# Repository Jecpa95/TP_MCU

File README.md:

# TP_MCU

## TP MCU by Kévin OKONSKI et Jérôme DUPOUTS

--------------------------------------------------------------------------------------------------------------------------------------------------------------------

- PB9 est relié à la masse car cette PIN correspond à BOOT0. Ici ont relie à la masse afin que le BOOT se fasse dans la memoire Flash.

--------------------------------------------------------------------------------------------------------------------------------------------------------------------

- Le role de L1, C5 et C7 est de réaliser un filtre passe bas pour éliminer les parasites sur l'alimentation 3.3V. On utilise par la suite cette tension au niveau de VDDA qui est la PIN de l'ADC

--------------------------------------------------------------------------------------------------------------------------------------------------------------------

--------------------------------------------------------------------------------------------------------------------------------------------------------------------

- C'est la première page qui indique les valeurs des condensateurs, mais on retrouve à la page 1 les valeurs typiques : 

--------------------------------------------------------------------------------------------------------------------------------------------------------------------

- C'est à la page 25 que l'on retrouve l'information : 

--------------------------------------------------------------------------------------------------------------------------------------------------------------------

- CS signifie Chip Select et permet d'activer la communication SPI, elle est valide à l'état Bas

--------------------------------------------------------------------------------------------------------------------------------------------------------------------

- la PIN LDAC (latch DAC synchronization input) permet de transféré l'entrée à la sortie du DAC. Lorsque l'entrée est à l'état bas la sortie recopie l'entrée.

--------------------------------------------------------------------------------------------------------------------------------------------------------------------

- Le MCP n'est pas activé car on ne renvoie pas d'information au STM32.

--------------------------------------------------------------------------------------------------------------------------------------------------------------------

- On retrouve les indications du PinOut du connecteur SWD dans la documentation du STlink à la page 17

--------------------------------------------------------------------------------------------------------------------------------------------------------------------

--------------------------------------------------------------------------------------------------------------------------------------------------------------------

- Ces valeurs est une indiquation sur la tailles des différents composants

--------------------------------------------------------------------------------------------------------------------------------------------------------------------

- Les boîtiers Dummy Low Profile Quad Flat Pack (LQFP) sont des types de boitiers de circuit intégré destiné à être directement soudé sur un circuit imprimé.

--------------------------------------------------------------------------------------------------------------------------------------------------------------------

--------------------------------------------------------------------------------------------------------------------------------------------------------------------

- 
on choisit donc un prescaler à 125, (32000000/1000)/256

--------------------------------------------------------------------------------------------------------------------------------------------------------------------

- nous avons choisie les même valeurs que pour TIM2 pour avoir une fréquence d'intéruption de 1kHz, donc le Prescaler vaut 125 et ARR 255

--------------------------------------------------------------------------------------------------------------------------------------------------------------------

La fonction est vide
--------------------------------------------------------------------------------------------------------------------------------------------------------------------

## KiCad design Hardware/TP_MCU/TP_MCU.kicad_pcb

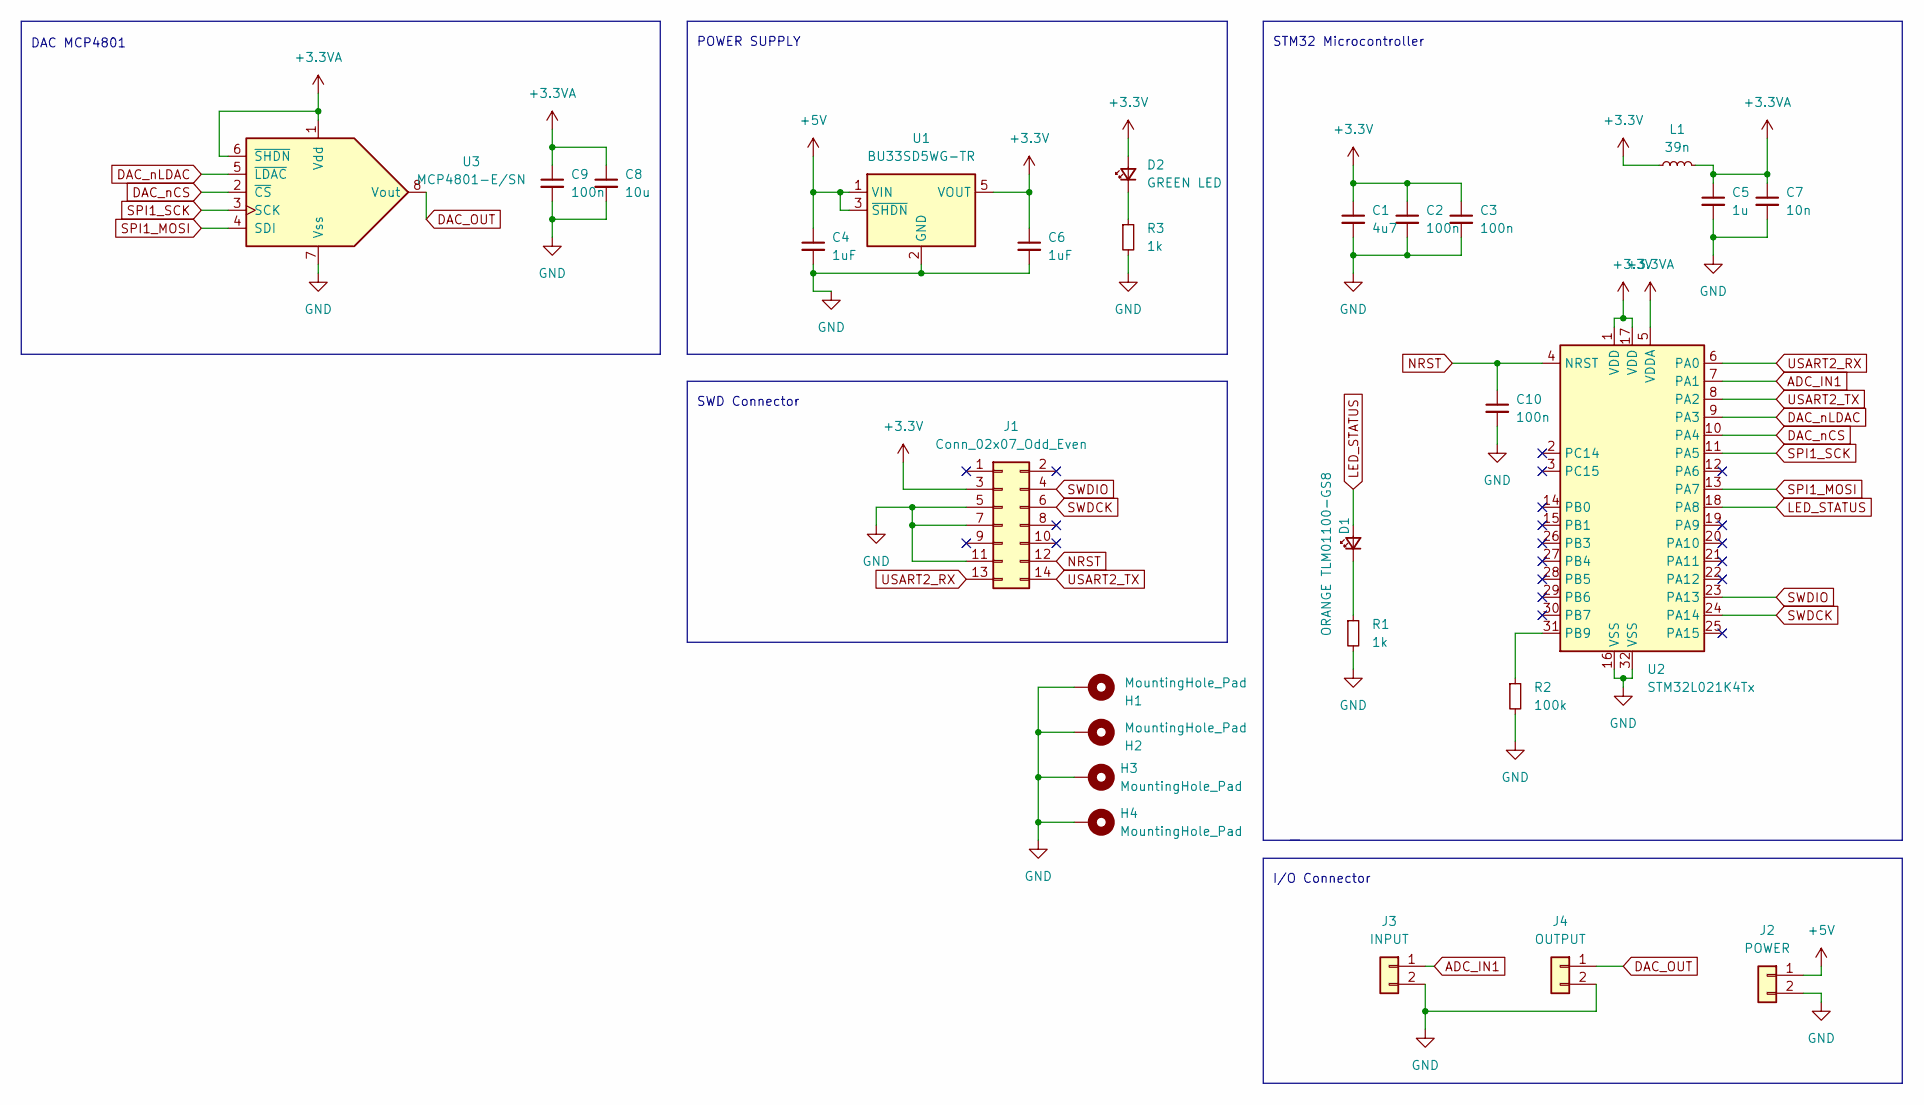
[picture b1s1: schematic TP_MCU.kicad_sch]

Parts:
C1: 4u7; C_0805_2012Metric
C2, C3, C9, C10: 100n; C_0805_2012Metric
C4, C6: 1uF; C_0805_2012Metric
C5: 1u; C_0805_2012Metric
C7: 10n; C_0805_2012Metric
C8: 10u; C_0805_2012Metric
D1: ORANGE TLM01100-GS8; LED_0603_1608Metric
D2: GREEN LED; LED_0603_1608Metric
H1, H2, H3, H4: MountingHole_Pad; MountingHole_3.2mm_M3_Pad
J1: Conn_02x07_Odd_Even; PinHeader_2x07_P1.27mm_Vertical_SMD
J2: POWER; JST_XH_B2B-XH-A_1x02_P2.50mm_Vertical
J3: INPUT; JST_XH_B2B-XH-A_1x02_P2.50mm_Vertical
J4: OUTPUT; JST_XH_B2B-XH-A_1x02_P2.50mm_Vertical
L1: 39n; L_0805_2012Metric
R1, R3: 1k; R_0805_2012Metric
R2: 100k; R_0805_2012Metric
U1: BU33SD5WG-TR; SOT-23-5
U2: STM32L021K4Tx; LQFP-32_7x7mm_P0.8mm
U3: MCP4801-E/SN; SOIC-8_3.9x4.9mm_P1.27mm

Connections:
+3.3V: C1.1, C2.1, C3.1, C6.1, D2.2 (A), J1.3, L1.2, U1.5 (VOUT), U2.1 (VDD), U2.17 (VDD)
+5V: C4.1, J2.1, U1.1 (VIN), U1.3 (~SHDN)
ADC_IN1: J3.1, U2.7 (PA1)
DAC_OUT: J4.1, U3.8 (Vout)
DAC_nCS: U2.10 (PA4), U3.2 (~CS)
DAC_nLDAC: U2.9 (PA3), U3.5 (~LDAC)
GND: C1.2, C2.2, C3.2, C4.2, C5.2, C6.2, C7.2, C8.2, C9.2, C10.2, H1.1, H2.1, H3.1, H4.1, J1.5, J1.7, J1.11, J2.2, J3.2, J4.2, R1.2, R2.2, R3.2, U1.2 (GND), U2.16 (VSS), U2.32 (VSS), U3.7 (Vss)
LED_STATUS: D1.2 (A), U2.18 (PA8)
NRST: C10.1, J1.12, U2.4 (NRST)
unnamed: D1.1 (K), R1.1
unnamed: D2.1 (K), R3.1
unnamed: R2.1, U2.31 (PB9)
SPI1_MOSI: U2.13 (PA7), U3.4 (SDI)
SPI1_SCK: U2.11 (PA5), U3.3 (SCK)
SWDCK: J1.6, U2.24 (PA14)
SWDIO: J1.4, U2.23 (PA13)
USART2_RX: J1.13, U2.6 (PA0)
USART2_TX: J1.14, U2.8 (PA2)

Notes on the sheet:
I/O Connector
DAC MCP4801
SWD Connector
STM32 Microcontroller
POWER SUPPLY

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
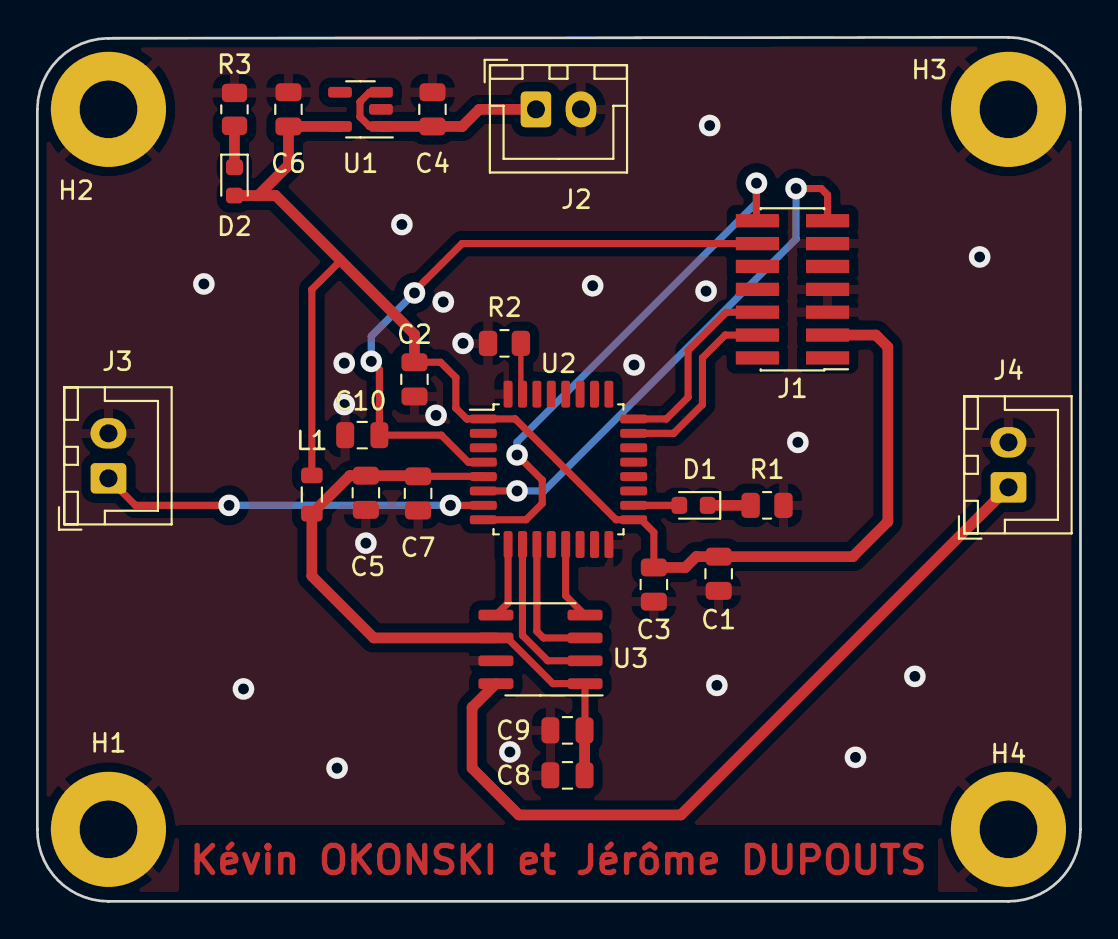
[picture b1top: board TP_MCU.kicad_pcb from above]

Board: 2 copper layers, 58.0 x 48.0 mm, 27 parts (0 on the bottom side), 19 nets.

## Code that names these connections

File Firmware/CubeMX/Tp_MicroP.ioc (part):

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Mcu.Name=STM32L021K4Tx
Mcu.Package=LQFP32
Mcu.UserName=STM32L021K4Tx
PA0-CK_IN.Mode=Asynchronous
PA0-CK_IN.Signal=USART2_RX
PA1.Mode=IN1
PA1.Signal=ADC_IN1
PA13.Mode=Serial_Wire
PA13.Signal=SYS_SWDIO
PA14.Mode=Serial_Wire
PA14.Signal=SYS_SWCLK
PA2.Mode=Asynchronous
PA2.Signal=USART2_TX
PA3.GPIOParameters=GPIO_Label
PA3.GPIO_Label=DAC_nLDAC
PA3.Signal=GPIO_Output
PA4.GPIOParameters=GPIO_Label
PA4.GPIO_Label=DAC_nCS
PA4.Signal=GPIO_Output
PA5.Mode=Full_Duplex_Master
PA5.Signal=SPI1_SCK
PA6.Mode=Full_Duplex_Master
PA6.Signal=SPI1_MISO
PA7.Mode=Full_Duplex_Master
PA7.Signal=SPI1_MOSI
PA8.Signal=S_TIM2_CH1
RCC.HSE_VALUE=8000000
RCC.SYSCLKFreq_VALUE=32000000
RCC.SYSCLKSource=RCC_SYSCLKSOURCE_PLLCLK
board=custom

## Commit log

2023-02-15 Create Test
2023-02-15 Create test1
2023-02-15 Create Datasheet site
2023-03-08 Premier ajout
